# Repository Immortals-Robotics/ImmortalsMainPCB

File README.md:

# Immortals Main Electronics
The main electronics of Immortals SSL robots, used to receive commands from the main computer through wireless link, drive the robots’ motors, apply a control loop on the motors, do some local sensing and send some feedback data to the main computer.

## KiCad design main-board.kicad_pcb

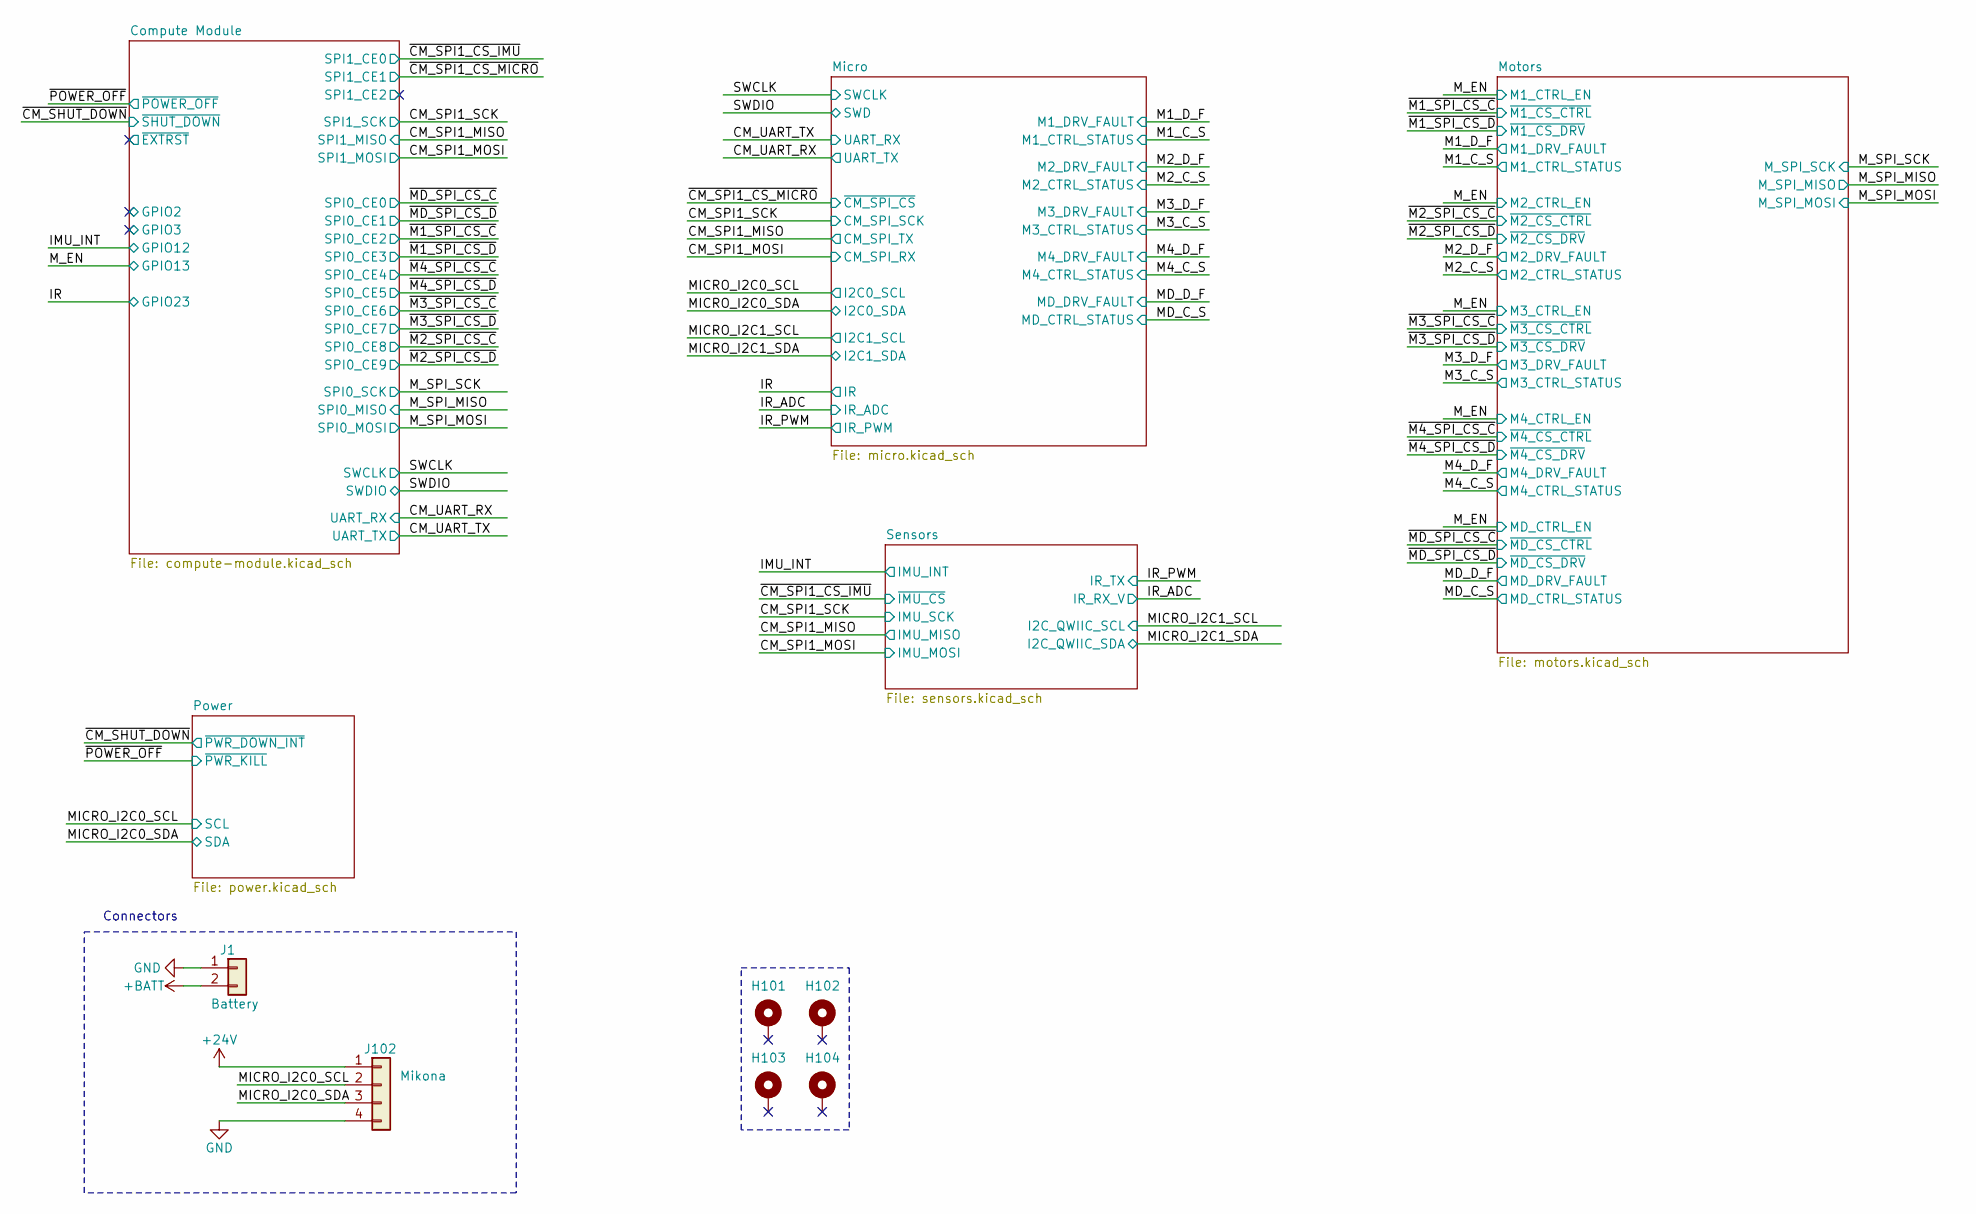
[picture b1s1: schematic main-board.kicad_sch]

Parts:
H101, H102, H103, H104: MountingHole_Pad; MountingHole_3.2mm_M3_ISO14580_Pad
J1: Battery; AMASS_XT60PW-M_1x02_P7.20mm_Horizontal; MPN XT60PW-M
J102: Mikona; MOLEX_1054301204; MPN 1054301204

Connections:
/MICRO_I2C0_SCL: J102.2; also elsewhere on the board
/MICRO_I2C0_SDA: J102.3; also elsewhere on the board

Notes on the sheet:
Connectors

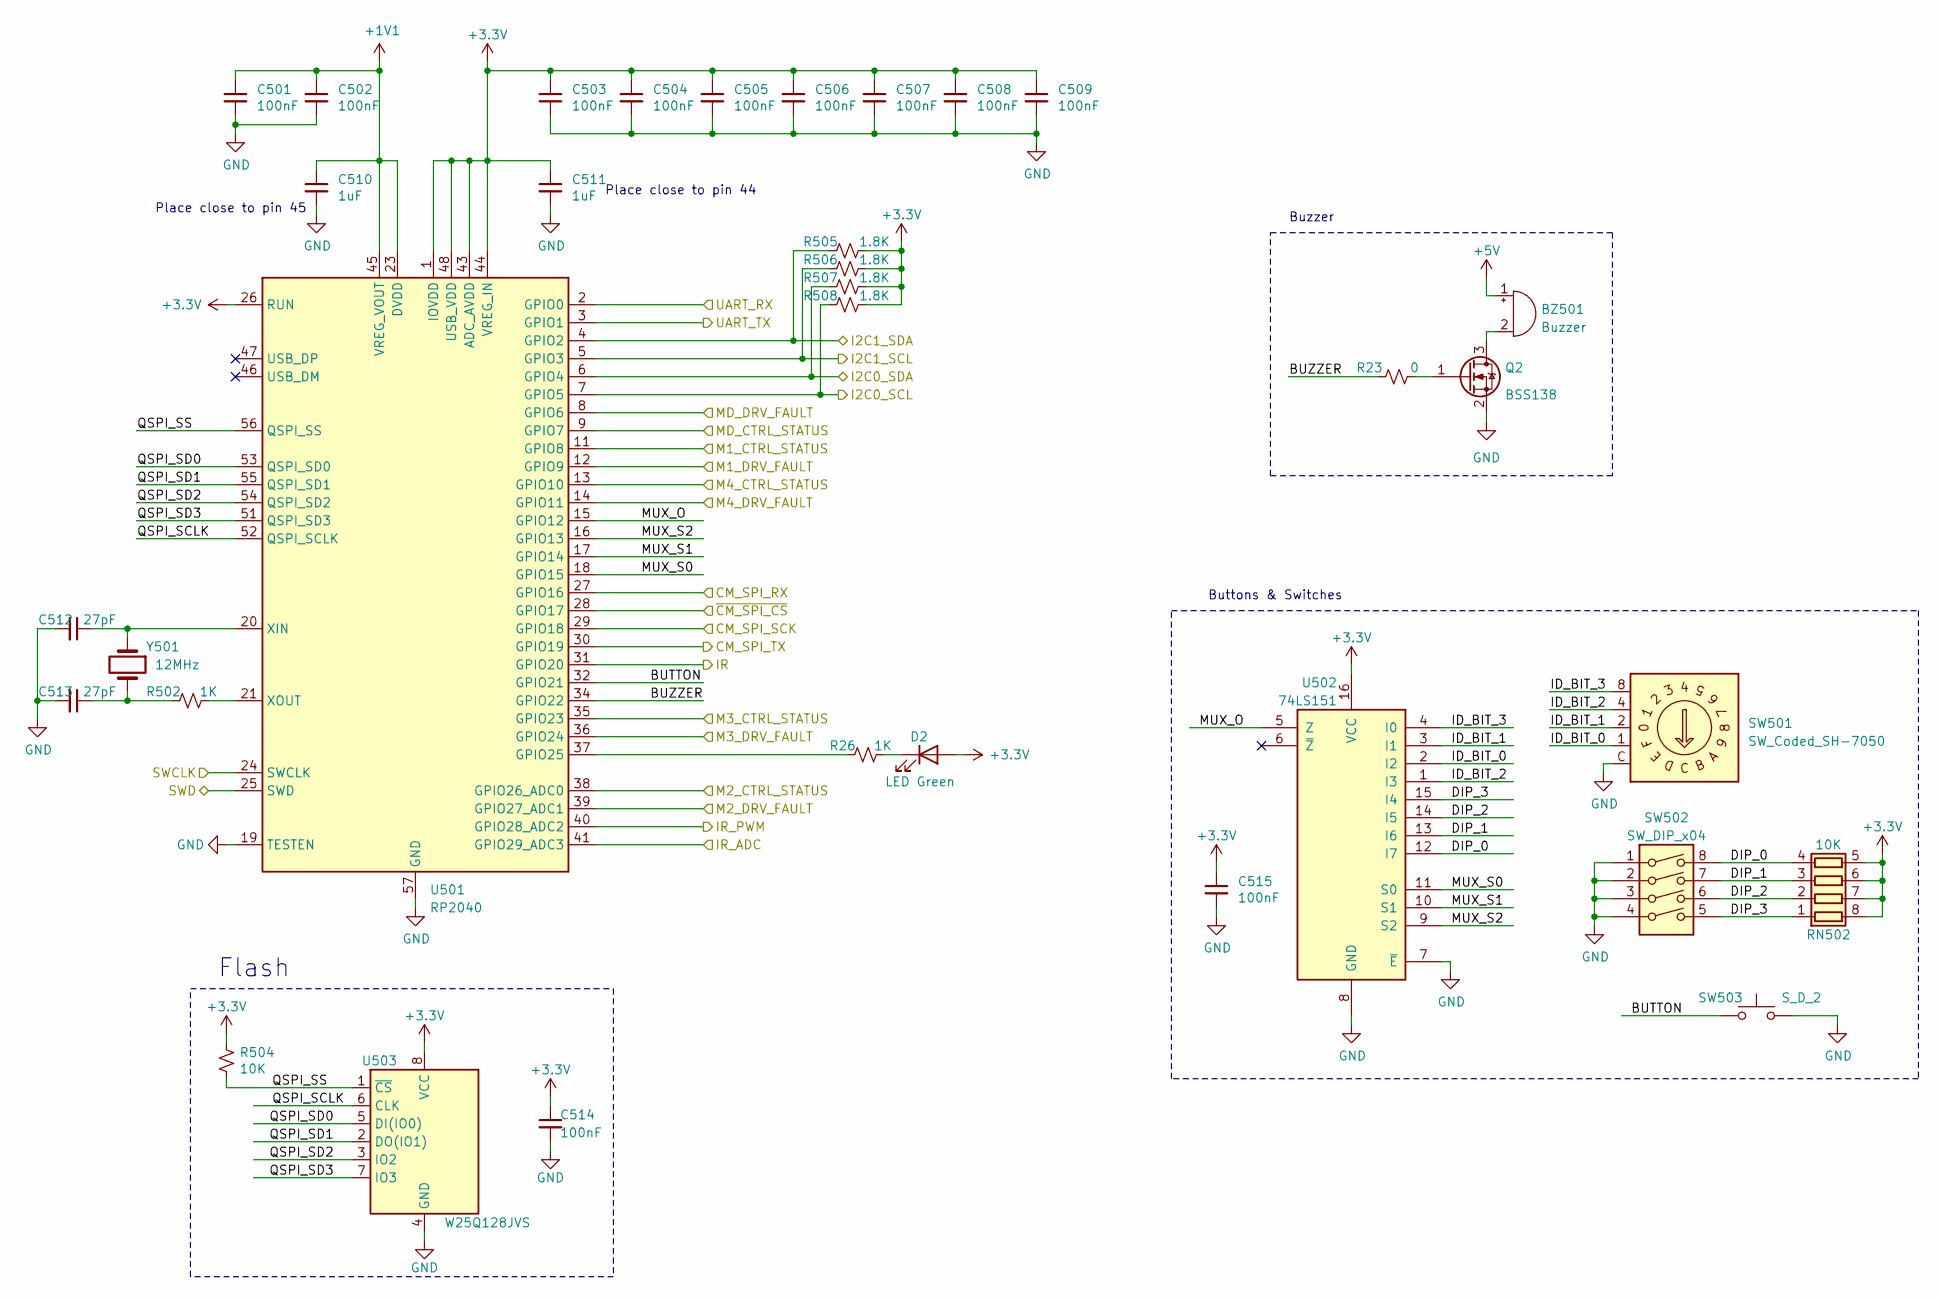
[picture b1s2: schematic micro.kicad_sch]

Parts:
BZ501: Buzzer; MagneticBuzzer_CUI_CMT-8504-100-SMT; MPN ST-03BHT
C501, C502, C503, C504, C505, C506, C507, C508, C509, C514, C515: 100nF; C_0603_1608Metric; MPN RM EMK105 B7104KV-F
C510, C511: 1uF; C_0603_1608Metric
C512, C513: 27pF; C_0603_1608Metric
D2: LED Green; LED_0603_1608Metric; MPN SML-A12M8TT86N
Q2: BSS138; SOT-23
R23: 0; R_0603_1608Metric; MPN RMCF0603ZT0R00
R26: 1K; R_0603_1608Metric; MPN RC0603FR-101KL
R502: 1K; R_0603_1608Metric
R504: 10K; R_0603_1608Metric
R505, R506, R507, R508: 1.8K; R_0603_1608Metric
RN502: 10K; R_Array_Concave_4x0603
SW501: SW_Coded_SH-7050; Nidec_Copal_SH-7010A; MPN SH-7050TA
SW502: SW_DIP_x04; SW_DIP_SPSTx04_Slide_6.7x11.72mm_W6.73mm_P2.54mm_LowProfile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; MPN 219-4MST
SW503: S_D_2; SW_Push_1P1T_NO_6x6mm_H9.5mm
U501: RP2040; QFN-56-1EP_7x7mm_P0.4mm_EP3.2x3.2mm
U502: 74LS151; SOIC-16_3.9x9.9mm_P1.27mm; MPN 74HC151D
U503: W25Q128JVS; SOIC-8_5.23x5.23mm_P1.27mm
Y501: 12MHz; Crystal_SMD_5032-2Pin_5.0x3.2mm; MPN 445C25D12M00000

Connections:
+1V1: C501.1, C502.1, C510.1, U501.23 (DVDD), U501.45 (VREG_VOUT), U501.50 (DVDD)
+5V: BZ501.1 (-); also elsewhere on the board
/CM_SPI1_MISO: U501.30 (GPIO19); also elsewhere on the board
/CM_SPI1_MOSI: U501.27 (GPIO16); also elsewhere on the board
/CM_SPI1_SCK: U501.29 (GPIO18); also elsewhere on the board
/CM_UART_RX: U501.3 (GPIO1); also elsewhere on the board
/CM_UART_TX: U501.2 (GPIO0); also elsewhere on the board
/IR: U501.31 (GPIO20); also elsewhere on the board
/IR_ADC: U501.41 (GPIO29_ADC3); also elsewhere on the board
/IR_PWM: U501.40 (GPIO28_ADC2); also elsewhere on the board
/M1_C_S: U501.11 (GPIO8); also elsewhere on the board
/M1_D_F: U501.12 (GPIO9); also elsewhere on the board
/M2_C_S: U501.38 (GPIO26_ADC0); also elsewhere on the board
/M2_D_F: U501.39 (GPIO27_ADC1); also elsewhere on the board
/M3_C_S: U501.35 (GPIO23); also elsewhere on the board
/M3_D_F: U501.36 (GPIO24); also elsewhere on the board
/M4_C_S: U501.13 (GPIO10); also elsewhere on the board
/M4_D_F: U501.14 (GPIO11); also elsewhere on the board
/MD_C_S: U501.9 (GPIO7); also elsewhere on the board
/MD_D_F: U501.8 (GPIO6); also elsewhere on the board
/MICRO_I2C0_SCL: R508.2, U501.7 (GPIO5); also elsewhere on the board
/MICRO_I2C0_SDA: R507.2, U501.6 (GPIO4); also elsewhere on the board
/MICRO_I2C1_SCL: R506.2, U501.5 (GPIO3); also elsewhere on the board
/MICRO_I2C1_SDA: R505.2, U501.4 (GPIO2); also elsewhere on the board
/Micro/BUTTON: SW503.1, U501.32 (GPIO21)
/Micro/BUZZER: U501.34 (GPIO22); also elsewhere on the board
/Micro/DIP_0: RN502.4 (R4.1), SW502.8, U502.12 (I7)
/Micro/DIP_1: RN502.3 (R3.1), SW502.7, U502.13 (I6)
/Micro/DIP_2: RN502.2 (R2.1), SW502.6, U502.14 (I5)
/Micro/DIP_3: RN502.1 (R1.1), SW502.5, U502.15 (I4)
/Micro/ID_BIT_0: SW501.1, U502.2 (I2)
/Micro/ID_BIT_1: SW501.2, U502.3 (I1)
/Micro/ID_BIT_2: SW501.4, U502.1 (I3)
/Micro/ID_BIT_3: SW501.8, U502.4 (I0)
/Micro/MUX_O: U501.15 (GPIO12), U502.5 (Z)
/Micro/MUX_S0: U501.18 (GPIO15), U502.11 (S0)
/Micro/MUX_S1: U501.17 (GPIO14), U502.10 (S1)
/Micro/MUX_S2: U501.16 (GPIO13), U502.9 (S2)
/Micro/QSPI_SCLK: U501.52 (QSPI_SCLK), U503.6 (CLK)
/Micro/QSPI_SD0: U501.53 (QSPI_SD0), U503.5 (DI(IO0))
/Micro/QSPI_SD1: U501.55 (QSPI_SD1), U503.2 (DO(IO1))
/Micro/QSPI_SD2: U501.54 (QSPI_SD2), U503.3 (IO2)
/Micro/QSPI_SD3: U501.51 (QSPI_SD3), U503.7 (IO3)
/Micro/QSPI_SS: R504.2, U501.56 (QSPI_SS), U503.1 (~CS)
/SWCLK: U501.24 (SWCLK); also elsewhere on the board
/SWDIO: U501.25 (SWD); also elsewhere on the board
/~CM_SPI1_CS_MICRO: U501.28 (GPIO17); also elsewhere on the board
unnamed 136: BZ501.2 (+); also elsewhere on the board
unnamed: C513.1, R502.2, Y501.2
unnamed 167: U501.37 (GPIO25); also elsewhere on the board
unnamed: C512.1, U501.20 (XIN), Y501.1
unnamed: R502.1, U501.21 (XOUT)

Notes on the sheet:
Place close to pin 44
Flash
Place close to pin 45
Buttons & Switches
Buzzer

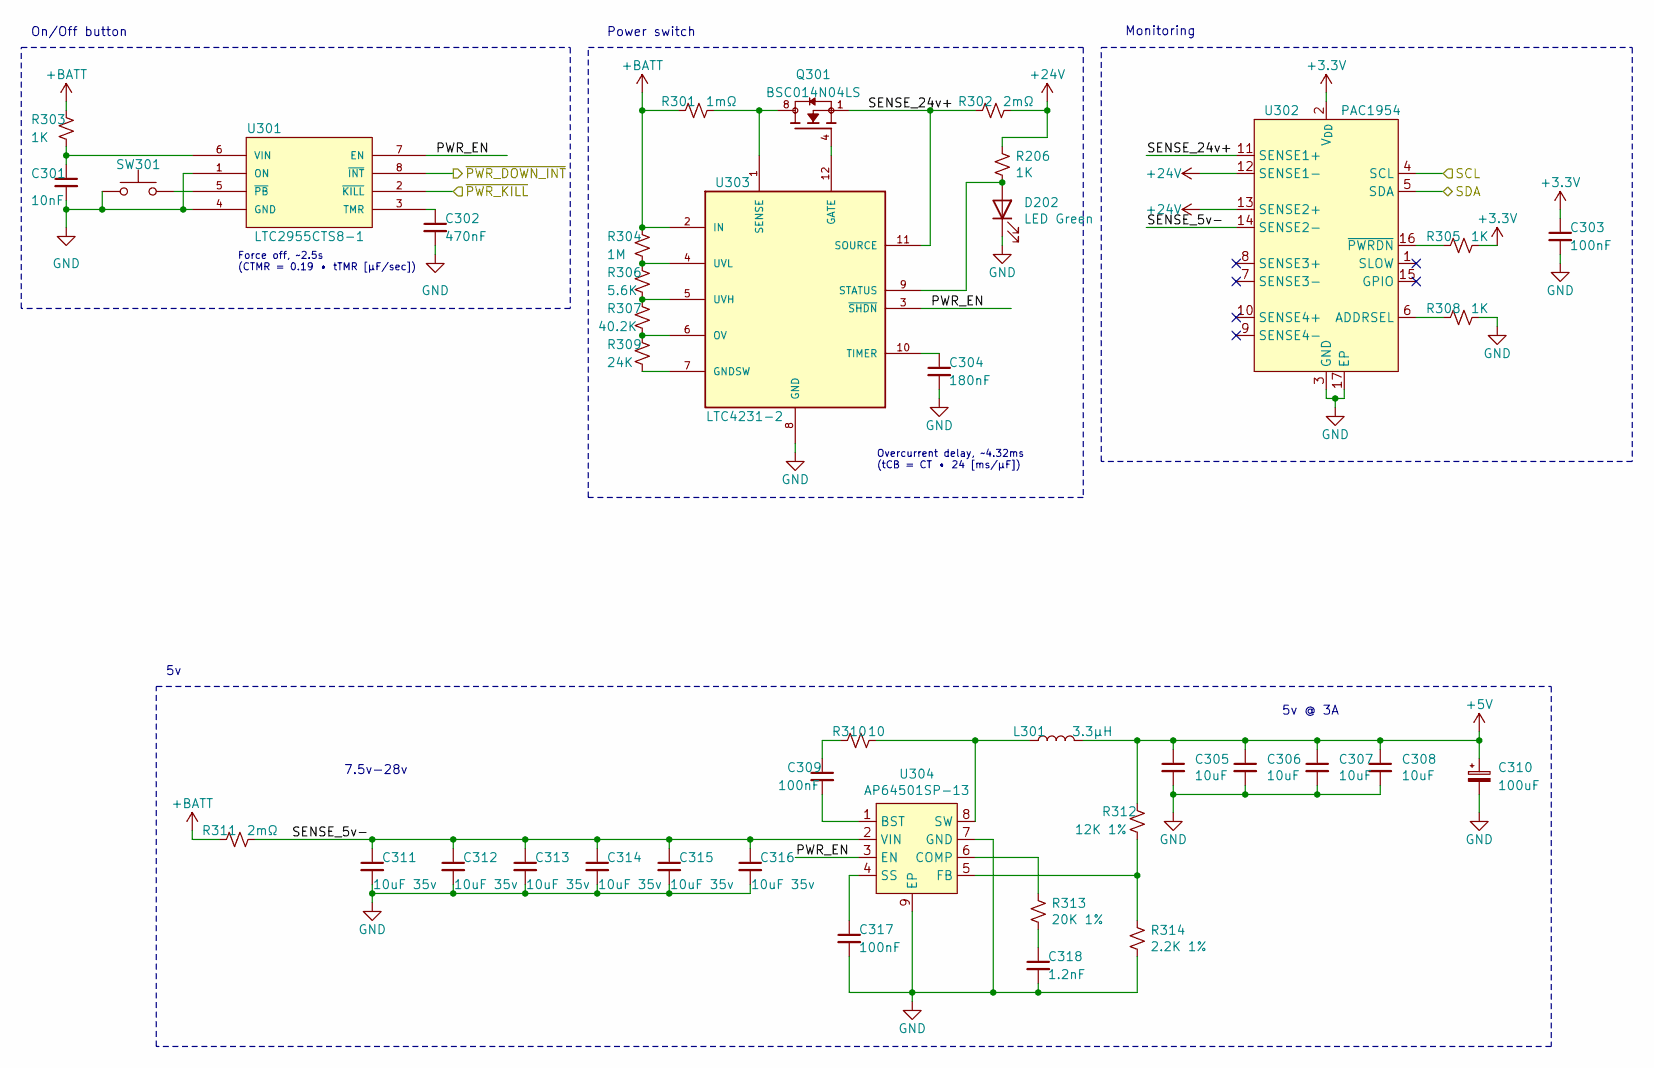
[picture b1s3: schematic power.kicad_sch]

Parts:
C301: 10nF; C_0805_2012Metric
C302: 470nF; C_0603_1608Metric
C303, C309, C317: 100nF; C_0603_1608Metric; MPN RM EMK105 B7104KV-F
C304: 180nF; C_0603_1608Metric
C305, C306, C307, C308: 10uF; C_0805_2012Metric; MPN GRM21BR71A106KA73L
C310: 100uF; CP_EIA-7343-31_Kemet-D
C311, C312, C313, C314, C315, C316: 10uF 35v; C_0805_2012Metric; MPN GRM21BC8YA106KE11L
C318: 1.2nF; C_0603_1608Metric; MPN GCM155R71H122KA37D
D202: LED Green; LED_0603_1608Metric; MPN SML-A12M8TT86N
L301: 3.3µH; L_Bourns_SRN6045TA; MPN SRN6045TA-3R3Y
Q301: BSC014N04LS; TRANS_BSC014N04LSIATMA1; MPN BSC014N04LSIATMA1
R206, R303, R305, R308: 1K; R_0603_1608Metric; MPN RC0603FR-101KL
R301: 1mΩ; R_2512_6332Metric
R302, R311: 2mΩ; R_2512_6332Metric
R304: 1M; R_0603_1608Metric
R306: 5.6K; R_0603_1608Metric
R307: 40.2K; R_0603_1608Metric
R309: 24K; R_0603_1608Metric
R310: 10; R_0603_1608Metric; MPN RC0402FR-0710RL
R312: 12K 1%; R_0603_1608Metric; MPN MCR01MZPF1202
R313: 20K 1%; R_0603_1608Metric; MPN RK73H1ETTP2002F
R314: 2.2K 1%; R_0603_1608Metric; MPN RK73G1ETQTP2201D
SW301: SW_Push; SW_Tactile_SPST_Angled_PTS645Vx58-2LFS; MPN 1825027-8
U301: LTC2955CTS8-1; TSOT-23-8
U302: PAC1954; VQFN-16-1EP_3x3mm_P0.5mm_EP1.1x1.1mm
U303: LTC4231-2; MSOP-12_3x4mm_P0.65mm
U304: AP64501SP-13; SOIC-8-1EP_3.9x4.9mm_P1.27mm_EP2.62x3.51mm; MPN AP64501SP-13

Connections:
+5V: C305.1, C306.1, C307.1, C308.1, C310.1, L301.2, R312.1; also elsewhere on the board
+BATT: R301.2, R303.1, R304.1, R311.2, U303.2 (IN); also elsewhere on the board
/MICRO_I2C0_SCL: U302.4 (SCL); also elsewhere on the board
/MICRO_I2C0_SDA: U302.5 (SDA); also elsewhere on the board
/Power/PWR_EN: U301.7 (EN), U303.3 (~SHDN), U304.3 (EN)
/Power/SENSE_5v-: C311.1, C312.1, C313.1, C314.1, C315.1, C316.1, R311.1, U302.14 (SENSE2-), U304.2 (VIN)
/Power/SENSE_24v+: Q301.1, R302.2, U302.11 (SENSE1+), U303.11 (SOURCE)
/~CM_SHUT_DOWN: U301.8 (~INT); also elsewhere on the board
/~POWER_OFF: U301.2 (~KILL); also elsewhere on the board
unnamed: C309.1, R310.2
unnamed: C318.1, R313.2
unnamed: C302.1, U301.3 (TMR)
unnamed: C301.1, R303.2, U301.6 (VIN)
unnamed: SW301.2, U301.5 (~PB)
unnamed: R308.2, U302.6 (ADDRSEL)
unnamed: R305.2, U302.16 (~PWRDN)
unnamed: Q301.4, U303.12 (GATE)
unnamed: R309.2, U303.7 (GNDSW)
unnamed: R307.2, R309.1, U303.6 (OV)
unnamed: Q301.8, R301.1, U303.1 (SENSE)
unnamed: C304.1, U303.10 (TIMER)
unnamed: R306.2, R307.1, U303.5 (UVH)
unnamed: R304.2, R306.1, U303.4 (UVL)
unnamed: C309.2, U304.1 (BST)
unnamed: R313.1, U304.6 (COMP)
unnamed: R312.2, R314.1, U304.5 (FB)
unnamed: C317.1, U304.4 (SS)
unnamed: L301.1, R310.1, U304.8 (SW)

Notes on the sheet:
5v @ 3A
Force off, ~2.5s (CTMR = 0.19 • tTMR [µF/sec])
Monitoring
Overcurrent delay, ~4.32ms (tCB = CT • 24 [ms/µF])
Power switch
7.5v-28v
On/Off button

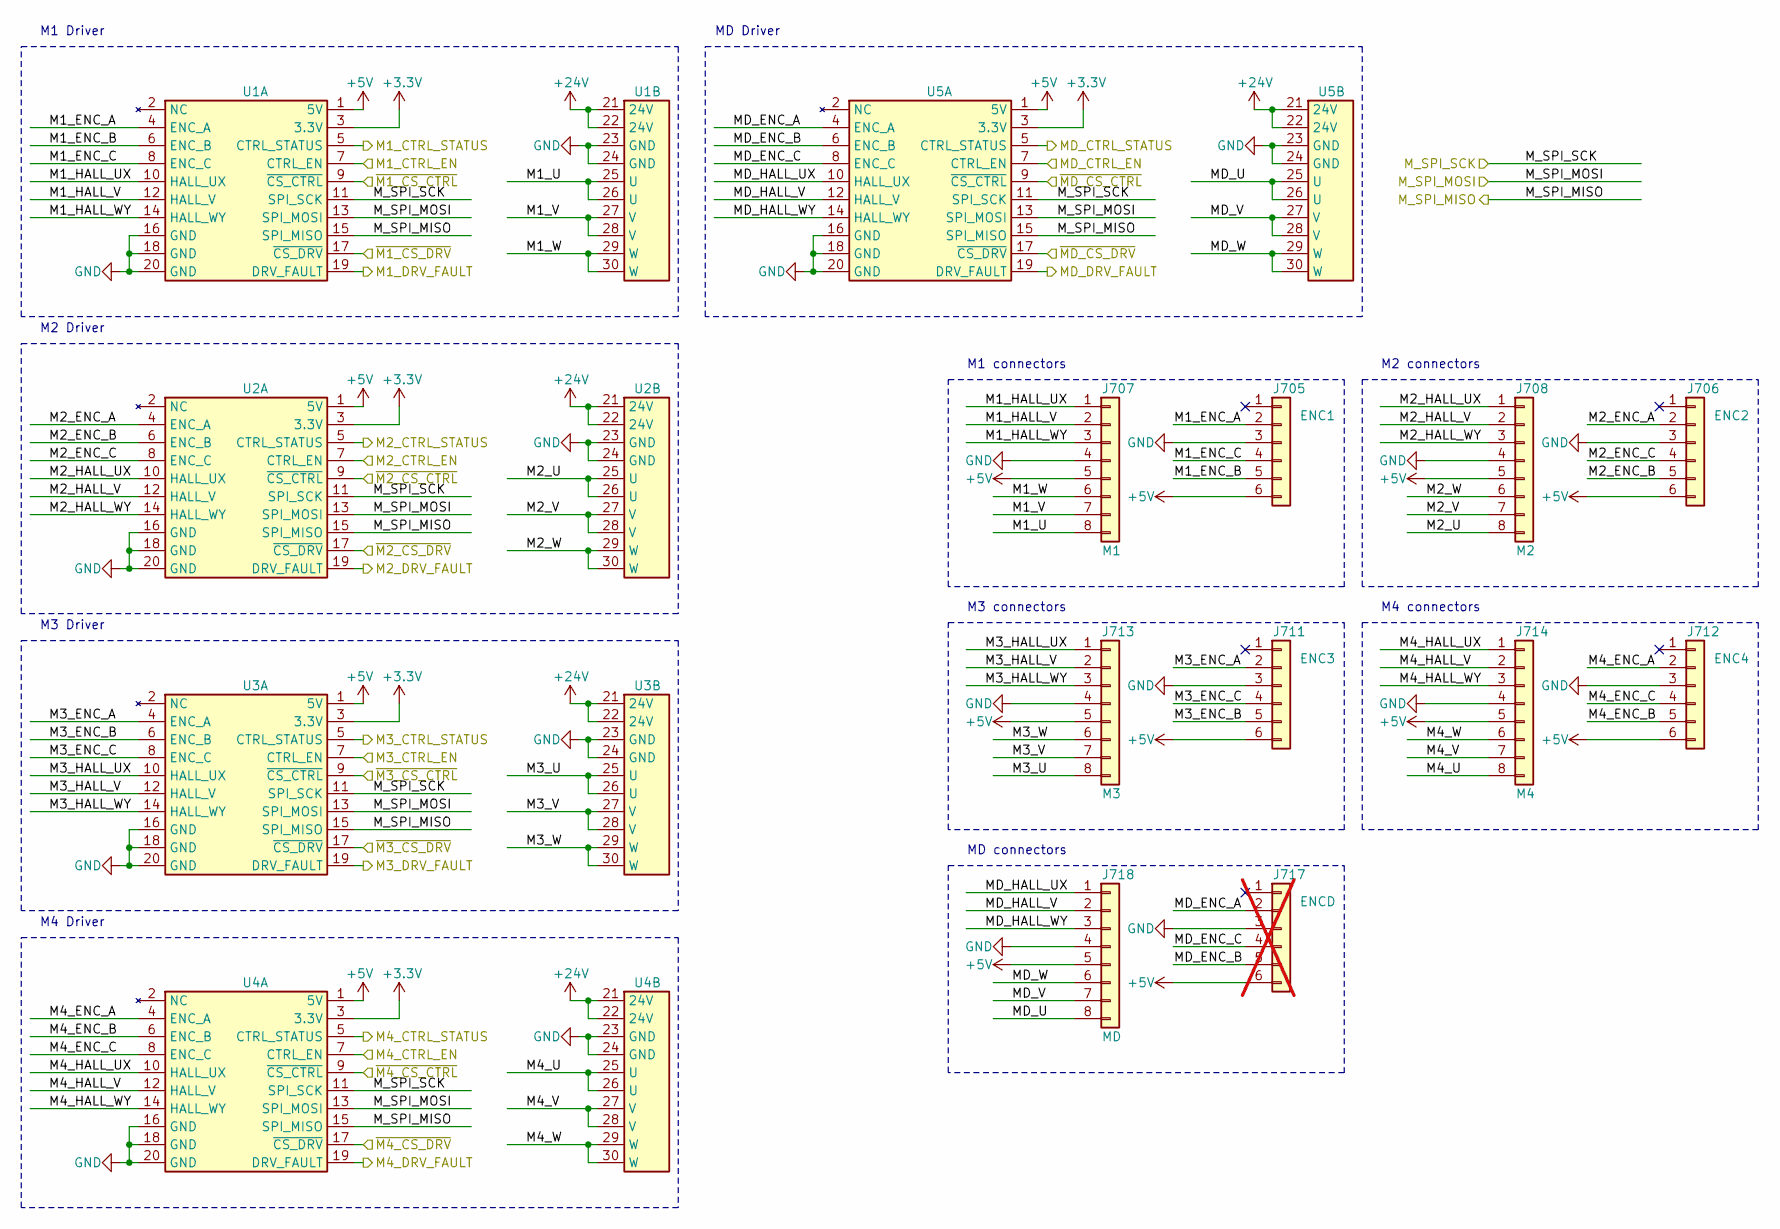
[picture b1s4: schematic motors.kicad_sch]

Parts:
J705: ENC1; Molex_PicoBlade_53261-0671_1x06-1MP_P1.25mm_Horizontal
J706: ENC2; Molex_PicoBlade_53261-0671_1x06-1MP_P1.25mm_Horizontal
J707: M1; JST_XH_S8B-XH-A_1x08_P2.50mm_Horizontal; MPN S8B-XH-A(LF)(SN)
J708: M2; JST_XH_S8B-XH-A_1x08_P2.50mm_Horizontal; MPN S8B-XH-A(LF)(SN)
J711: ENC3; Molex_PicoBlade_53261-0671_1x06-1MP_P1.25mm_Horizontal
J712: ENC4; Molex_PicoBlade_53261-0671_1x06-1MP_P1.25mm_Horizontal
J713: M3; JST_XH_S8B-XH-A_1x08_P2.50mm_Horizontal; MPN S8B-XH-A(LF)(SN)
J714: M4; JST_XH_S8B-XH-A_1x08_P2.50mm_Horizontal; MPN S8B-XH-A(LF)(SN)
J717: ENCD; Molex_PicoBlade_53261-0671_1x06-1MP_P1.25mm_Horizontal; not fitted
J718: MD; JST_XH_S8B-XH-A_1x08_P2.50mm_Horizontal; MPN S8B-XH-A(LF)(SN)
U1, U2, U3, U4, U5: MotorDriver-SMT

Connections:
+5V: J705.6, J706.6, J707.5, J708.5, J711.6, J712.6, J713.5, J714.5, J717.6, J718.5, U1.1 (5V), U2.1 (5V), U3.1 (5V), U4.1 (5V), U5.1 (5V); also elsewhere on the board
/M1_C_S: U1.5 (CTRL_STATUS); also elsewhere on the board
/M1_D_F: U1.19 (DRV_FAULT); also elsewhere on the board
/M2_C_S: U2.5 (CTRL_STATUS); also elsewhere on the board
/M2_D_F: U2.19 (DRV_FAULT); also elsewhere on the board
/M3_C_S: U3.5 (CTRL_STATUS); also elsewhere on the board
/M3_D_F: U3.19 (DRV_FAULT); also elsewhere on the board
/M4_C_S: U4.5 (CTRL_STATUS); also elsewhere on the board
/M4_D_F: U4.19 (DRV_FAULT); also elsewhere on the board
/MD_C_S: U5.5 (CTRL_STATUS); also elsewhere on the board
/MD_D_F: U5.19 (DRV_FAULT); also elsewhere on the board
/M_EN: U1.7 (CTRL_EN), U2.7 (CTRL_EN), U3.7 (CTRL_EN), U4.7 (CTRL_EN), U5.7 (CTRL_EN); also elsewhere on the board
/M_SPI_MISO: U1.15 (SPI_MISO), U2.15 (SPI_MISO), U3.15 (SPI_MISO), U4.15 (SPI_MISO), U5.15 (SPI_MISO); also elsewhere on the board
/M_SPI_MOSI: U1.13 (SPI_MOSI), U2.13 (SPI_MOSI), U3.13 (SPI_MOSI), U4.13 (SPI_MOSI), U5.13 (SPI_MOSI); also elsewhere on the board
/M_SPI_SCK: U1.11 (SPI_SCK), U2.11 (SPI_SCK), U3.11 (SPI_SCK), U4.11 (SPI_SCK), U5.11 (SPI_SCK); also elsewhere on the board
/Motors/M1_ENC_A: J705.2, U1.4 (ENC_A)
/Motors/M1_ENC_B: J705.5, U1.6 (ENC_B)
/Motors/M1_ENC_C: J705.4, U1.8 (ENC_C)
/Motors/M1_HALL_UX: J707.1, U1.10 (HALL_UX)
/Motors/M1_HALL_V: J707.2, U1.12 (HALL_V)
/Motors/M1_HALL_WY: J707.3, U1.14 (HALL_WY)
/Motors/M1_U: J707.8, U1.25 (U), U1.26 (U)
/Motors/M1_V: J707.7, U1.27 (V), U1.28 (V)
/Motors/M1_W: J707.6, U1.29 (W), U1.30 (W)
/Motors/M2_ENC_A: J706.2, U2.4 (ENC_A)
/Motors/M2_ENC_B: J706.5, U2.6 (ENC_B)
/Motors/M2_ENC_C: J706.4, U2.8 (ENC_C)
/Motors/M2_HALL_UX: J708.1, U2.10 (HALL_UX)
/Motors/M2_HALL_V: J708.2, U2.12 (HALL_V)
/Motors/M2_HALL_WY: J708.3, U2.14 (HALL_WY)
/Motors/M2_U: J708.8, U2.25 (U), U2.26 (U)
/Motors/M2_V: J708.7, U2.27 (V), U2.28 (V)
/Motors/M2_W: J708.6, U2.29 (W), U2.30 (W)
/Motors/M3_ENC_A: J711.2, U3.4 (ENC_A)
/Motors/M3_ENC_B: J711.5, U3.6 (ENC_B)
/Motors/M3_ENC_C: J711.4, U3.8 (ENC_C)
/Motors/M3_HALL_UX: J713.1, U3.10 (HALL_UX)
/Motors/M3_HALL_V: J713.2, U3.12 (HALL_V)
/Motors/M3_HALL_WY: J713.3, U3.14 (HALL_WY)
/Motors/M3_U: J713.8, U3.25 (U), U3.26 (U)
/Motors/M3_V: J713.7, U3.27 (V), U3.28 (V)
/Motors/M3_W: J713.6, U3.29 (W), U3.30 (W)
/Motors/M4_ENC_A: J712.2, U4.4 (ENC_A)
/Motors/M4_ENC_B: J712.5, U4.6 (ENC_B)
/Motors/M4_ENC_C: J712.4, U4.8 (ENC_C)
/Motors/M4_HALL_UX: J714.1, U4.10 (HALL_UX)
/Motors/M4_HALL_V: J714.2, U4.12 (HALL_V)
/Motors/M4_HALL_WY: J714.3, U4.14 (HALL_WY)
/Motors/M4_U: J714.8, U4.25 (U), U4.26 (U)
/Motors/M4_V: J714.7, U4.27 (V), U4.28 (V)
/Motors/M4_W: J714.6, U4.29 (W), U4.30 (W)
/Motors/MD_ENC_A: J717.2, U5.4 (ENC_A)
/Motors/MD_ENC_B: J717.5, U5.6 (ENC_B)
/Motors/MD_ENC_C: J717.4, U5.8 (ENC_C)
/Motors/MD_HALL_UX: J718.1, U5.10 (HALL_UX)
/Motors/MD_HALL_V: J718.2, U5.12 (HALL_V)
/Motors/MD_HALL_WY: J718.3, U5.14 (HALL_WY)
/Motors/MD_U: J718.8, U5.25 (U), U5.26 (U)
/Motors/MD_V: J718.7, U5.27 (V), U5.28 (V)
/Motors/MD_W: J718.6, U5.29 (W), U5.30 (W)
/~M1_SPI_CS_C: U1.9 (~CS_CTRL); also elsewhere on the board
/~M1_SPI_CS_D: U1.17 (~CS_DRV); also elsewhere on the board
/~M2_SPI_CS_C: U2.9 (~CS_CTRL); also elsewhere on the board
/~M2_SPI_CS_D: U2.17 (~CS_DRV); also elsewhere on the board
/~M3_SPI_CS_C: U3.9 (~CS_CTRL); also elsewhere on the board
/~M3_SPI_CS_D: U3.17 (~CS_DRV); also elsewhere on the board
/~M4_SPI_CS_C: U4.9 (~CS_CTRL); also elsewhere on the board
/~M4_SPI_CS_D: U4.17 (~CS_DRV); also elsewhere on the board
/~MD_SPI_CS_C: U5.9 (~CS_CTRL); also elsewhere on the board
/~MD_SPI_CS_D: U5.17 (~CS_DRV); also elsewhere on the board

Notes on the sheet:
MD connectors
M1 connectors
M3 connectors
M1 Driver
M4 Driver
M2 Driver
M2 connectors
MD Driver
M3 Driver
M4 connectors

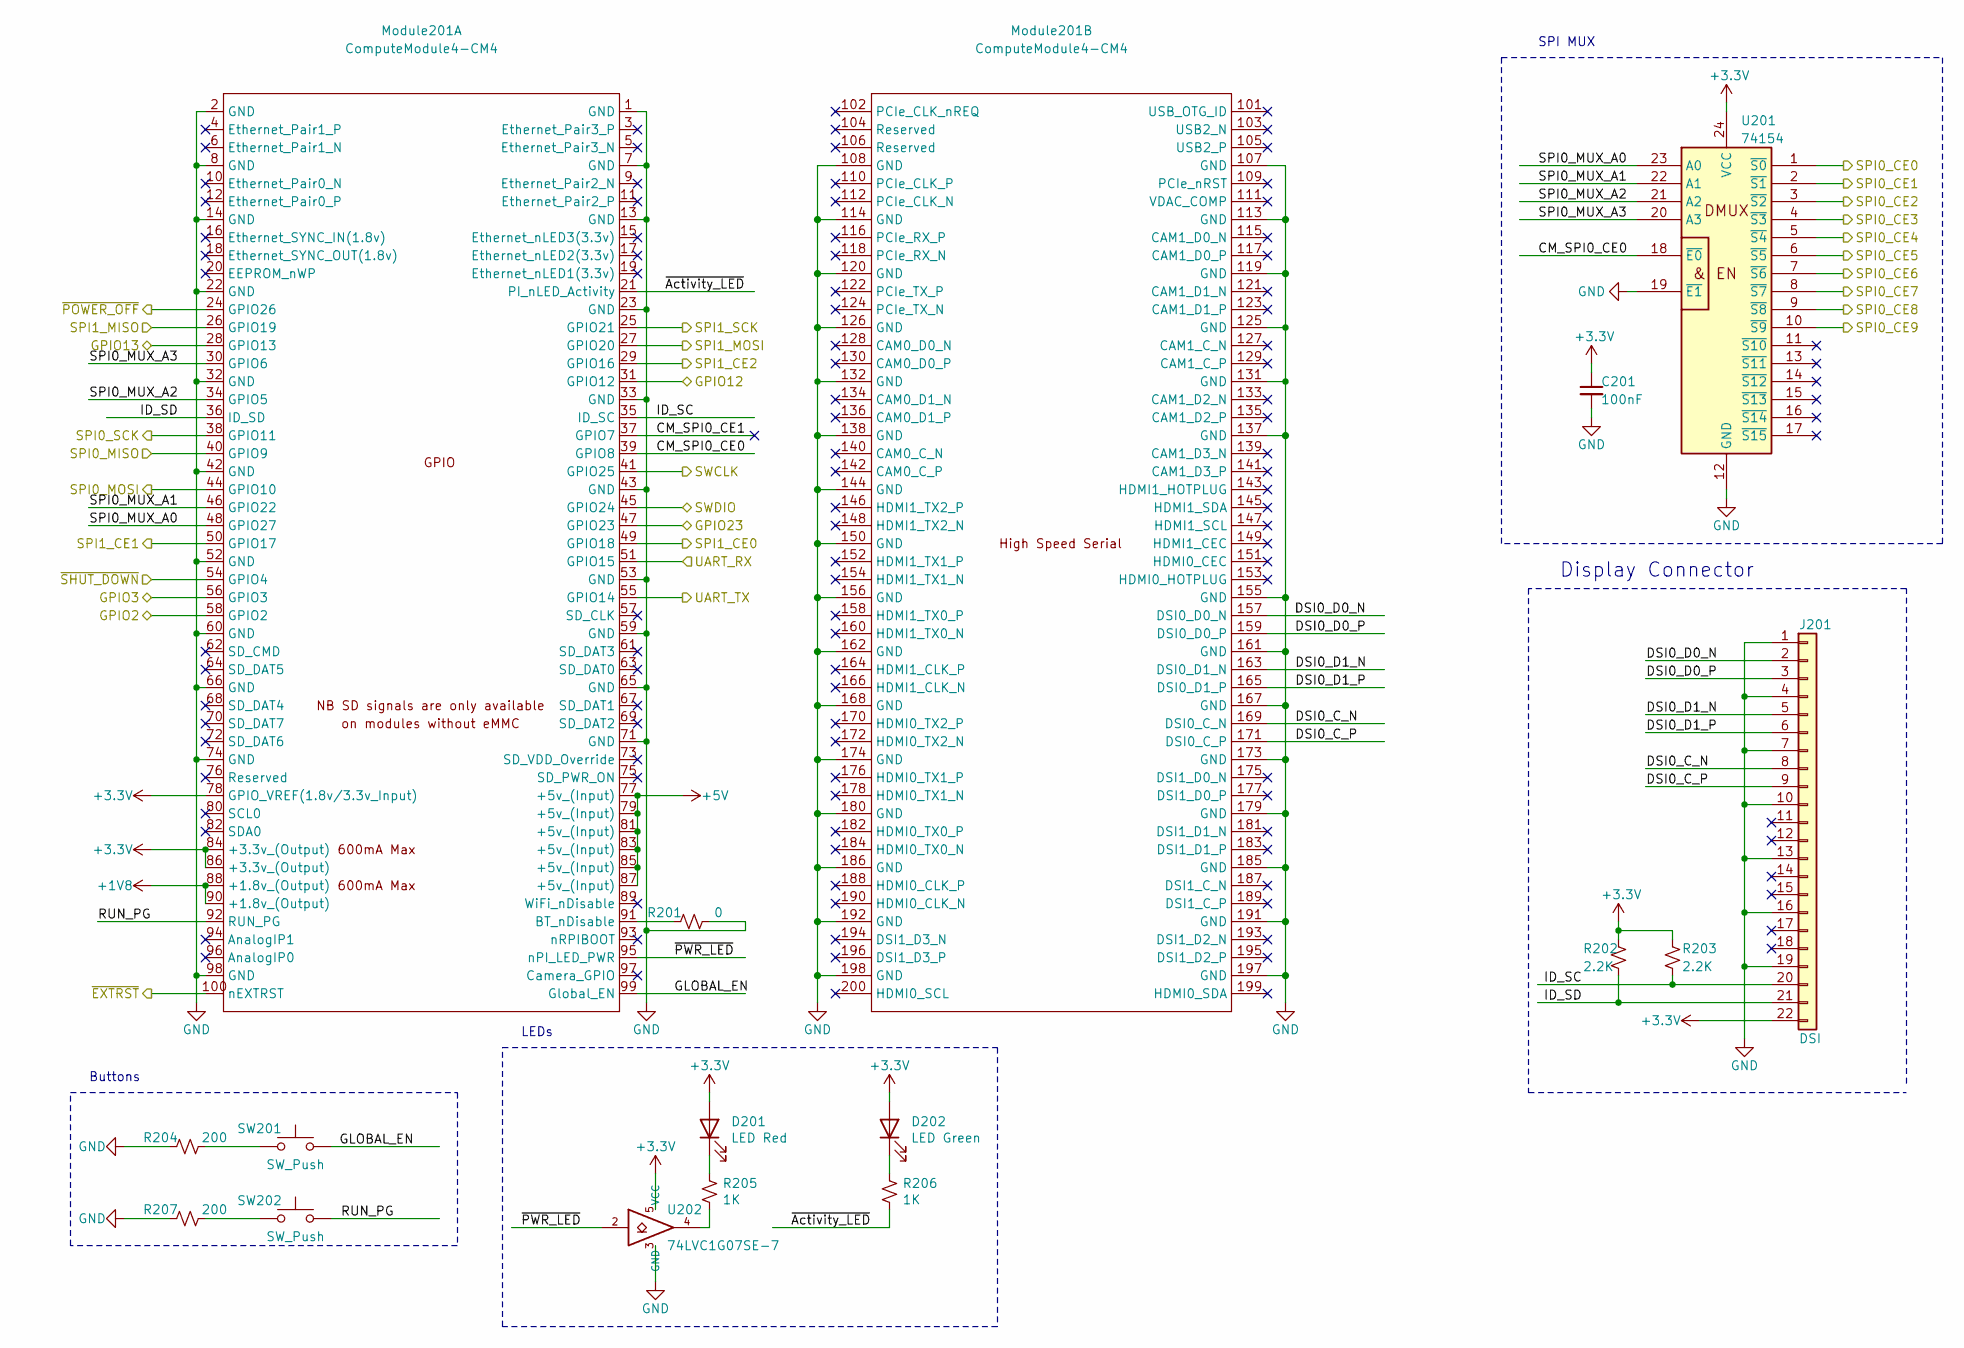
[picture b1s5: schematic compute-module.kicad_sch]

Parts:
C201: 100nF; C_0603_1608Metric; MPN RM EMK105 B7104KV-F
D201: LED Red; LED_0603_1608Metric; MPN SML-A12U8TT86Q
D202: LED Green; LED_0603_1608Metric; MPN SML-A12M8TT86N
J201: DSI; Hirose_FH12-22S-0.5SH_1x22-1MP_P0.50mm_Horizontal; MPN FH12-22S-0.5SH55
Module201: ComputeModule4-CM4; rpi-cm4
R201: 0; R_0603_1608Metric; MPN RMCF0603ZT0R00
R202, R203: 2.2K; R_0603_1608Metric; MPN RC0603FR-132K2L
R204, R207: 200; R_0603_1608Metric; MPN RC0603FR-13200RL
R205, R206: 1K; R_0603_1608Metric; MPN RC0603FR-101KL
SW201, SW202: SW_Push; SW_SPST_B3U-1000P; MPN TS04-66-65-BK-100-SMT
U201: 74154; DHVQFN24; MPN 74HCT154BQ,118
U202: 74LVC1G07SE-7; SOT-353_SC-70-5; MPN 74LVC1G07SE-7

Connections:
+1V8: Module201.88 (+1.8v_(Output)), Module201.90 (+1.8v_(Output))
+5V: Module201.77 (+5v_(Input)), Module201.79 (+5v_(Input)), Module201.81 (+5v_(Input)), Module201.83 (+5v_(Input)), Module201.85 (+5v_(Input)), Module201.87 (+5v_(Input)); also elsewhere on the board
/CM_SPI1_MISO: Module201.26 (GPIO19); also elsewhere on the board
/CM_SPI1_MOSI: Module201.27 (GPIO20); also elsewhere on the board
/CM_SPI1_SCK: Module201.25 (GPIO21); also elsewhere on the board
/CM_UART_RX: Module201.51 (GPIO15); also elsewhere on the board
/CM_UART_TX: Module201.55 (GPIO14); also elsewhere on the board
/Compute Module/CM_SPI0_CE0: Module201.39 (GPIO8), U201.18 (~E0)
/Compute Module/CM_SPI0_CE1: Module201.37 (GPIO7)
/Compute Module/DSI0_C_N: J201.8, Module201.169 (DSI0_C_N)
/Compute Module/DSI0_C_P: J201.9, Module201.171 (DSI0_C_P)
/Compute Module/DSI0_D0_N: J201.2, Module201.157 (DSI0_D0_N)
/Compute Module/DSI0_D0_P: J201.3, Module201.159 (DSI0_D0_P)
/Compute Module/DSI0_D1_N: J201.5, Module201.163 (DSI0_D1_N)
/Compute Module/DSI0_D1_P: J201.6, Module201.165 (DSI0_D1_P)
/Compute Module/GLOBAL_EN: Module201.99 (Global_EN), SW201.2
/Compute Module/GPIO2: Module201.58 (GPIO2)
/Compute Module/GPIO3: Module201.56 (GPIO3)
/Compute Module/ID_SC: J201.20, Module201.35 (ID_SC), R203.2
/Compute Module/ID_SD: J201.21, Module201.36 (ID_SD), R202.2
/Compute Module/RUN_PG: Module201.92 (RUN_PG), SW202.2
/Compute Module/SPI0_MUX_A0: Module201.48 (GPIO27), U201.23 (A0)
/Compute Module/SPI0_MUX_A1: Module201.46 (GPIO22), U201.22 (A1)
/Compute Module/SPI0_MUX_A2: Module201.34 (GPIO5), U201.21 (A2)
/Compute Module/SPI0_MUX_A3: Module201.30 (GPIO6), U201.20 (A3)
/Compute Module/SPI1_CE2: Module201.29 (GPIO16)
/Compute Module/~EXTRST: Module201.100 (nEXTRST)
/Compute Module/~PWR_LED: Module201.95 (nPI_LED_PWR), U202.2
/IMU_INT: Module201.31 (GPIO12); also elsewhere on the board
/IR: Module201.47 (GPIO23); also elsewhere on the board
/M_EN: Module201.28 (GPIO13); also elsewhere on the board
/M_SPI_MISO: Module201.40 (GPIO9); also elsewhere on the board
/M_SPI_MOSI: Module201.44 (GPIO10); also elsewhere on the board
/M_SPI_SCK: Module201.38 (GPIO11); also elsewhere on the board
/SWCLK: Module201.41 (GPIO25); also elsewhere on the board
/SWDIO: Module201.45 (GPIO24); also elsewhere on the board
/~CM_SHUT_DOWN: Module201.54 (GPIO4); also elsewhere on the board
/~CM_SPI1_CS_IMU: Module201.49 (GPIO18); also elsewhere on the board
/~CM_SPI1_CS_MICRO: Module201.50 (GPIO17); also elsewhere on the board
/~M1_SPI_CS_C: U201.3 (~S2); also elsewhere on the board
/~M1_SPI_CS_D: U201.4 (~S3); also elsewhere on the board
/~M2_SPI_CS_C: U201.9 (~S8); also elsewhere on the board
/~M2_SPI_CS_D: U201.10 (~S9); also elsewhere on the board
/~M3_SPI_CS_C: U201.7 (~S6); also elsewhere on the board
/~M3_SPI_CS_D: U201.8 (~S7); also elsewhere on the board
/~M4_SPI_CS_C: U201.5 (~S4); also elsewhere on the board
/~M4_SPI_CS_D: U201.6 (~S5); also elsewhere on the board
/~MD_SPI_CS_C: U201.1 (~S0); also elsewhere on the board
/~MD_SPI_CS_D: U201.2 (~S1); also elsewhere on the board
/~POWER_OFF: Module201.24 (GPIO26); also elsewhere on the board
unnamed: D201.1 (K), R205.1
unnamed: Module201.91 (BT_nDisable), R201.1
unnamed: R204.2, SW201.1
unnamed: R205.2, U202.4
unnamed: R207.2, SW202.1

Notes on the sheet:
Display Connector
SPI MUX
Buttons
LEDs
